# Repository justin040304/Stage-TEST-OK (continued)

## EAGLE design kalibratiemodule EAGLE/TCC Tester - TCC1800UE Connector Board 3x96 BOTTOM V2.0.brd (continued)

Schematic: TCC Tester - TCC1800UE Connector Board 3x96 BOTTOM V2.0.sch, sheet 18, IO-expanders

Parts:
C40, C41: 100nF; C0603
IC1, IC2: MCP23017SO; SO28W
R124, R125, R126, R127, R128, R129, R130, R131, R132, R133, R134, R135: 0R; R0603
R136, R137, R138, R139, R140, R141, R142, R143, R144, R145, R146, R147, R148, R149, R150, R151, R190: 10K; R0603
TP3, TP4, TP5, TP6, TP7, TP8, TP9, TP10, TP11, TP12, TP13, TP14, TP15, TP16, TP19: PTR1TP13R; TP13R

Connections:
+3.3V: C40.1, C41.1, IC1.9 (VDD), IC1.18 (!RESET), IC2.9 (VDD), IC2.18 (!RESET), R124.2, R125.2, R126.2, R130.2, R131.2, R132.2, R136.2, R137.2, R138.2, R139.2, R140.2, R141.2, R142.2, R143.2, R144.2, R145.2, R146.2, R147.2, R148.2, R149.2, R150.2, R151.2, R190.2; also elsewhere on the board
GND: C40.2, C41.2, IC1.10 (VSS), IC2.10 (VSS), R127.2, R128.2, R129.2, R133.2, R134.2, R135.2; also elsewhere on the board
unnamed: IC1.22 (GPA1), TP3.TP
unnamed: IC1.23 (GPA2), TP19.TP
unnamed: IC1.25 (GPA4), TP5.TP
unnamed: IC1.26 (GPA5), TP6.TP
unnamed: IC1.27 (GPA6), TP7.TP
unnamed: IC1.28 (GPA7), TP8.TP
unnamed: IC1.1 (GPB0), TP9.TP
unnamed: IC1.2 (GPB1), TP10.TP
unnamed: IC1.3 (GPB2), TP11.TP
unnamed: IC1.4 (GPB3), TP12.TP
unnamed: IC1.5 (GPB4), TP13.TP
unnamed: IC1.6 (GPB5), TP14.TP
unnamed: IC1.7 (GPB6), TP15.TP
unnamed: IC1.8 (GPB7), TP16.TP
unnamed: IC1.24 (GPA3), TP4.TP
unnamed: IC2.15 (A0), R126.1, R127.1
unnamed: IC2.16 (A1), R124.1, R128.1
unnamed: IC2.17 (A2), R125.1, R129.1
unnamed: IC1.15 (A0), R132.1, R133.1
unnamed: IC1.16 (A1), R130.1, R134.1
unnamed: IC1.17 (A2), R131.1, R135.1
SCL3.3V1: IC1.12 (SCL), IC2.12 (SCL); also elsewhere on the board
SDA3.3V1: IC1.13 (SDA), IC2.13 (SDA); also elsewhere on the board
SS1.1: IC2.21 (GPA0), R136.1; also elsewhere on the board
SS1.2: IC2.22 (GPA1), R137.1; also elsewhere on the board
SS1.3: IC2.23 (GPA2), R138.1; also elsewhere on the board
SS1.4: IC2.24 (GPA3), R139.1; also elsewhere on the board
SS1.5: IC2.25 (GPA4), R140.1; also elsewhere on the board
SS1.6: IC2.26 (GPA5), R141.1; also elsewhere on the board
SS1.7: IC2.27 (GPA6), R142.1; also elsewhere on the board
SS1.8: IC2.28 (GPA7), R143.1; also elsewhere on the board
SS1.9: IC2.1 (GPB0), R144.1; also elsewhere on the board
SS1.10: IC2.2 (GPB1), R145.1; also elsewhere on the board
SS1.11: IC2.3 (GPB2), R146.1; also elsewhere on the board
SS1.12: IC2.4 (GPB3), R147.1; also elsewhere on the board
SS1.13: IC2.5 (GPB4), R148.1; also elsewhere on the board
SS1.14: IC2.6 (GPB5), R149.1; also elsewhere on the board
SS1.15: IC2.7 (GPB6), R150.1; also elsewhere on the board
SS1.16: IC2.8 (GPB7), R151.1; also elsewhere on the board
SS1.17: IC1.21 (GPA0), R190.1; also elsewhere on the board

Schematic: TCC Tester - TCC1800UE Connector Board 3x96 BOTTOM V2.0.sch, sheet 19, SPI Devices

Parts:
C20, C21: 100nF; C0603
R11: 10K; R0603
U6: TXB0104D; SOIC127P600X175-14N

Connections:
5V: C21.1, U6.14 (VCCB); also elsewhere on the board
+3.3V: C20.1, R11.2, U6.1 (VCCA); also elsewhere on the board
GND: C20.2, C21.2, U6.7 (GND); also elsewhere on the board
MISO2-3.3V: U6.2 (A1); also elsewhere on the board
MISO2-5V: U6.13 (B1); also elsewhere on the board
MOSI2-3.3V: U6.3 (A2); also elsewhere on the board
MOSI2-5V: U6.12 (B2); also elsewhere on the board
SCK2-3.3V: U6.4 (A3); also elsewhere on the board
SCK2-5V: U6.11 (B3); also elsewhere on the board
SPI2_OE: R11.1, U6.8 (OE); also elsewhere on the board
SS2.1-3.3V: U6.5 (A4); also elsewhere on the board
SS2.1-5V: U6.10 (B4); also elsewhere on the board

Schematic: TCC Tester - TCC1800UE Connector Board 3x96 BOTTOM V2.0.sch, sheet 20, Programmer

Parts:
C49: DNP (100nF); C0603
C50, C51, C52, C53, C54, C55, C59, C60: 100nF; C0603
C56: 10uF; C0603
C57, C58: 30pF; C0603
CN8: USB_CONNECTORUSB_A_S_RA_SMT; MULTICOMP_USB_A_S_RA_SMT
J2: RJ11-2L-B; RJ11-NO_SHIELD
LED89, LED90, LED91, LED92: LEDCHIPLED_0805; CHIPLED_0805
R186: 10K; R0603
R187: 200R; R0603
R188, R189, R191, R192: 2.2K; R0603
R193: 0R; R0603
R_PGC: RELAY-SPDT; SPDT_TE_PE014*
R_PGD: RELAY-SPDT; SPDT_TE_PE014*
R_VPP: RELAY-SPDT; SPDT_TE_PE014*
S2: DNP; TACTILE-PTH
U$27: PICKIT3_HOLDER; PICKIT3_HOLDER_STL_100X49_V01
U$91: PIC24FJ256GA110-I/PT; QFP40P1400X1400X120-100N
U$92: TSX-3225; SMD,3.2MM_X_2.5MM
U$93: MAX4820; TSSOP20

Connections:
5V: C60.1, LED89.A, LED90.A, LED91.A, R193.1, R_PGC.1 (A1), R_PGD.1 (A1), R_VPP.1 (A1), U$93.1 (VCC), U$93.15 (COM); also elsewhere on the board
+3.3V: C50.1, C51.1, C52.1, C53.1, C54.1, C55.1, C59.1, J2.2, R186.2, U$27.2 (VDD), U$91.2 (VDD_2), U$91.16 (VDD_3), U$91.29 (PMA6/VREF+/CN42/RA10), U$91.30 (AVDD), U$91.37 (VDD_4), U$91.46 (VDD_5), U$91.62 (VDD), U$91.86 (ENVREG); also elsewhere on the board
GND: C49.2, C50.2, C51.2, C52.2, C53.2, C54.2, C55.2, C56.2, C57.2, C58.2, C59.2, C60.2, CN8.4 (GND), CN8.SHIELD@1 (SHIELD), CN8.SHIELD@2 (SHIELD), J2.3, R192.2, S2.1, U$27.3 (VSS), U$91.15 (VSS), U$91.28 (VREF-/CN41/PMA7/RA9), U$91.31 (AVSS), U$91.36 (VSS_3), U$91.45 (VSS_5), U$91.65 (VSS_2), U$91.75 (VSS_4), U$92.2, U$92.4, U$93.9 (GND), U$93.12 (PGND), U$93.18 (PGND); also elsewhere on the board
MCLR2: C49.1, R186.1, R187.2, R_VPP.11, S2.3
MOSI1: U$93.5 (DIN); also elsewhere on the board
unnamed: R187.1, U$91.13 (~MCLR)
unnamed: C57.1, U$91.63 (OSC1/CLKI/CN23/RC12), U$92.1
unnamed: C58.1, U$91.64 (OSC2/CLKO/CN22/RC15), U$92.3
unnamed: R188.2, R_PGC.2 (A2), U$93.20 (OUT1)
unnamed: C56.1, U$91.85 (VCAP/VDDCORE)
unnamed: LED92.C, R192.1
unnamed: R_VPP.14, U$27.1 (!MCLR!_VPP)
unnamed: R_PGD.14, U$27.4 (PGD)
unnamed: LED92.A, U$91.99 (CN61/PMD3/RE3)
unnamed: LED89.C, R188.1
unnamed: LED90.C, R189.1
unnamed: R_PGC.14, U$27.5 (PGC)
unnamed: R193.2, U$93.2 (SET), U$93.3 (RESET)
unnamed: LED91.C, R191.1
unnamed: R191.2, R_VPP.2 (A2), U$93.17 (OUT3)
unnamed: R189.2, R_PGD.2 (A2), U$93.19 (OUT2)
PGEC2: R_PGC.11, U$91.24 (PGEC1/AN1/RP1/CN3/RB1)
PGED2: R_PGD.11, U$91.25 (PGED1/AN0/RP0/CN2/RB0)
PGM_CLK_1: J2.5, R_PGC.12; also elsewhere on the board
PGM_DATA_1: J2.4, R_PGD.12; also elsewhere on the board
PGM_VPP_1: J2.1, R_VPP.12; also elsewhere on the board
SCK1: U$93.6 (CLK); also elsewhere on the board
SS1.16: U$93.4 (CS); also elsewhere on the board
USB_D+: CN8.3 (D+); also elsewhere on the board
USB_D-: CN8.2 (D-); also elsewhere on the board
USB_VBUS: CN8.1 (VBUS); also elsewhere on the board

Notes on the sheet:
MICROCONTROLLER FOR TESTING PROGRAMMER
USB A Connector for PICKIT3
Programmer header for external use of programmer

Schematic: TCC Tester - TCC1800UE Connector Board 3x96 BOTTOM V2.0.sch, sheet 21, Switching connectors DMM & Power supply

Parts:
C13: 100nF; C0603
CN1, CN2, CN3, CN4: HIRSCHMANN_972358700_4MM_SOCKET
CN5: BNC_5-1634506-1; BNC_TYCO_5-1634506-1
LED1, LED2, LED3, LED94, LED95, LED96, LED114, LED115: LEDCHIPLED_0805; CHIPLED_0805
R20: 2K 500mW; R0805
R22: 94K; R0603
R23, R24, R26, R111, R113, R114, R183, R184: 2.2K; R0603
R175, R182: 0R; R0603
R_FLUKE_COMMON1: RELAY-SPDT; SPDT_TE_PE014*
R_FLUKE_GND: RELAY-SPDT; SPDT_TE_PE014*
R_FLUKE_VOLTAGE+: RELAY-SPDT; SPDT_TE_PE014*
R_KEITHLEY_VOLTAGE+: RELAY-SPDT; SPDT_TE_PE014*
R_KEITHLEY_VOLTAGE+_OPEN-DRAIN: RELAY-SPDT; SPDT_TE_PE014*
R_VOLTAGE_MEASUREMENT: RELAY-SPDT; SPDT_TE_PE014*
R_VOLTAGE_MEASUREMENT_GROUP1, R_VOLTAGE_MEASUREMENT_GROUP4: RELAY-SPDT; SPDT_TE_PE014*
U$158: MAX4820; TSSOP20

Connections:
5V: C13.1, LED1.A, LED2.A, LED3.A, LED94.A, LED95.A, LED96.A, LED114.A, LED115.A, R175.1, R_FLUKE_COMMON1.1 (A1), R_FLUKE_GND.1 (A1), R_FLUKE_VOLTAGE+.1 (A1), R_KEITHLEY_VOLTAGE+.1 (A1), R_KEITHLEY_VOLTAGE+_OPEN-DRAIN.1 (A1), R_VOLTAGE_MEASUREMENT.1 (A1), R_VOLTAGE_MEASUREMENT_GROUP1.1 (A1), R_VOLTAGE_MEASUREMENT_GROUP4.1 (A1), U$158.1 (VCC), U$158.15 (COM); also elsewhere on the board
FLUKE_COMMON1: R_FLUKE_COMMON1.11; also elsewhere on the board
FLUKE_VOLTAGE+: R_FLUKE_VOLTAGE+.11, R_VOLTAGE_MEASUREMENT.11, R_VOLTAGE_MEASUREMENT_GROUP1.11, R_VOLTAGE_MEASUREMENT_GROUP4.11; also elsewhere on the board
GND: C13.2, CN2.P$1, R20.2, R22.2, R182.2, R_FLUKE_GND.11, U$158.9 (GND), U$158.12 (PGND), U$158.18 (PGND); also elsewhere on the board
KEITHLEY_VOLTAGE+: R_KEITHLEY_VOLTAGE+.11; also elsewhere on the board
KEITHLEY_VOLTAGE+_OPEN-DRAIN: R_KEITHLEY_VOLTAGE+_OPEN-DRAIN.11; also elsewhere on the board
MOSI1: U$158.5 (DIN); also elsewhere on the board
unnamed: R23.2, R_VOLTAGE_MEASUREMENT.2 (A2), U$158.13 (OUT6)
unnamed: R24.2, R_VOLTAGE_MEASUREMENT_GROUP4.2 (A2), U$158.11 (OUT7)
unnamed: R22.1, R_VOLTAGE_MEASUREMENT.14
unnamed: LED1.C, R23.1
unnamed: LED2.C, R24.1
unnamed: R20.1, R_VOLTAGE_MEASUREMENT_GROUP4.14
unnamed: R26.2, R_VOLTAGE_MEASUREMENT_GROUP1.2 (A2), U$158.10 (OUT8)
unnamed: CN3.P$1, R_VOLTAGE_MEASUREMENT_GROUP1.14
unnamed: LED3.C, R26.1
unnamed: R175.2, U$158.2 (SET), U$158.3 (RESET)
unnamed: CN5.GND2 (GND), R_FLUKE_COMMON1.14, R_FLUKE_GND.14
unnamed: R113.2, R_FLUKE_COMMON1.2 (A2), U$158.16 (OUT4)
unnamed: R114.2, R_FLUKE_GND.2 (A2), U$158.14 (OUT5)
unnamed: LED94.C, R111.1
unnamed: CN5.A, R_FLUKE_VOLTAGE+.14
unnamed: R111.2, R_FLUKE_VOLTAGE+.2 (A2), U$158.17 (OUT3)
unnamed: LED95.C, R113.1
unnamed: LED96.C, R114.1
unnamed: R184.2, R_KEITHLEY_VOLTAGE+.2 (A2), U$158.20 (OUT1)
unnamed: CN1.P$1, R_KEITHLEY_VOLTAGE+.14, R_KEITHLEY_VOLTAGE+_OPEN-DRAIN.14
unnamed: R183.2, R_KEITHLEY_VOLTAGE+_OPEN-DRAIN.2 (A2), U$158.19 (OUT2)
unnamed: LED115.C, R184.1
unnamed: LED114.C, R183.1
unnamed: CN4.P$1, R182.1
SCK1: U$158.6 (CLK); also elsewhere on the board
SS1.17: U$158.4 (CS); also elsewhere on the board

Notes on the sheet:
KEITHLEY GND
FLUKE GND
POWER RESISTOR OR ELECTRONIC LOAD
FLUKE_GND

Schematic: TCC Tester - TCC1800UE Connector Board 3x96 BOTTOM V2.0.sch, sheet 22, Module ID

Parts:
C201, C202: 100nF/50V; C0805
C203: 100pF/25V; C0805
R201: 100R; R0805
RA0, RA1: 10K; R0805
RB0, RB1: 10K; R0805
RC0, RC1: 10K; R0805
RD0, RD1: 10K; R0805
RE0, RE1: 10K; R0805
RF0, RF1: 10K; R0805
RG0, RG1: 10K; R0805
RH0, RH1: 10K; R0805
RI0, RI1: 10K; R0805
RJ0, RJ1: 10K; R0805
RK0, RK1: 10K; R0805
RL0, RL1: 10K; R0805
RM0, RM1: 10K; R0805
RN0, RN1: 10K; R0805
U1, U2: 74HC165D; SO16
U$4, U$6, U$7, U$8, U$9, U$10: 3.4; DRILL_HOLE_SPA

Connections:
5V: C201.1, C202.1, RA1.2, RB1.2, RC1.2, RD1.2, RE1.2, RF1.2, RG1.2, RH1.2, RI1.2, RJ1.2, RK1.2, RL1.2, RM1.2, RN1.2, U1.6 (H), U1.16 (VCC), U2.16 (VCC); also elsewhere on the board
C_EXT_CLK: R201.2; also elsewhere on the board
C_EXT_IN: U1.9 (QH); also elsewhere on the board
C_EXT_LOAD: U1.1 (SH/!LD), U2.1 (SH/!LD); also elsewhere on the board
GND: C201.2, C202.2, C203.2, RA0.1, RB0.1, RC0.1, RD0.1, RE0.1, RF0.1, RG0.1, RH0.1, RI0.1, RJ0.1, RK0.1, RL0.1, RM0.1, RN0.1, U1.8 (GND), U1.15 (INH), U2.6 (H), U2.8 (GND), U2.10 (SER), U2.15 (INH); also elsewhere on the board
ID_A: RA0.2, RA1.1, U1.11 (A)
ID_A1: RH0.2, RH1.1, U2.11 (A)
ID_B: RB0.2, RB1.1, U1.12 (B)
ID_B1: RI0.2, RI1.1, U2.12 (B)
ID_C: RC0.2, RC1.1, U1.13 (C)
ID_C1: RJ0.2, RJ1.1, U2.13 (C)
ID_D: RD0.2, RD1.1, U1.14 (D)
ID_D1: RK0.2, RK1.1, U2.14 (D)
ID_E: RE0.2, RE1.1, U1.3 (E)
ID_E1: RL0.2, RL1.1, U2.3 (E)
ID_F: RF0.2, RF1.1, U1.4 (F)
ID_F1: RM0.2, RM1.1, U2.4 (F)
ID_SCK_BIS: C203.1, R201.1, U1.2 (CLK), U2.2 (CLK)
unnamed: RG0.2, RG1.1, U1.5 (G)
unnamed: RN0.2, RN1.1, U2.5 (G)
unnamed: U1.10 (SER), U2.9 (QH)

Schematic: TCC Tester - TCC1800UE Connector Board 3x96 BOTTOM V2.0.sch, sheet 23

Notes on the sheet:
TODO:

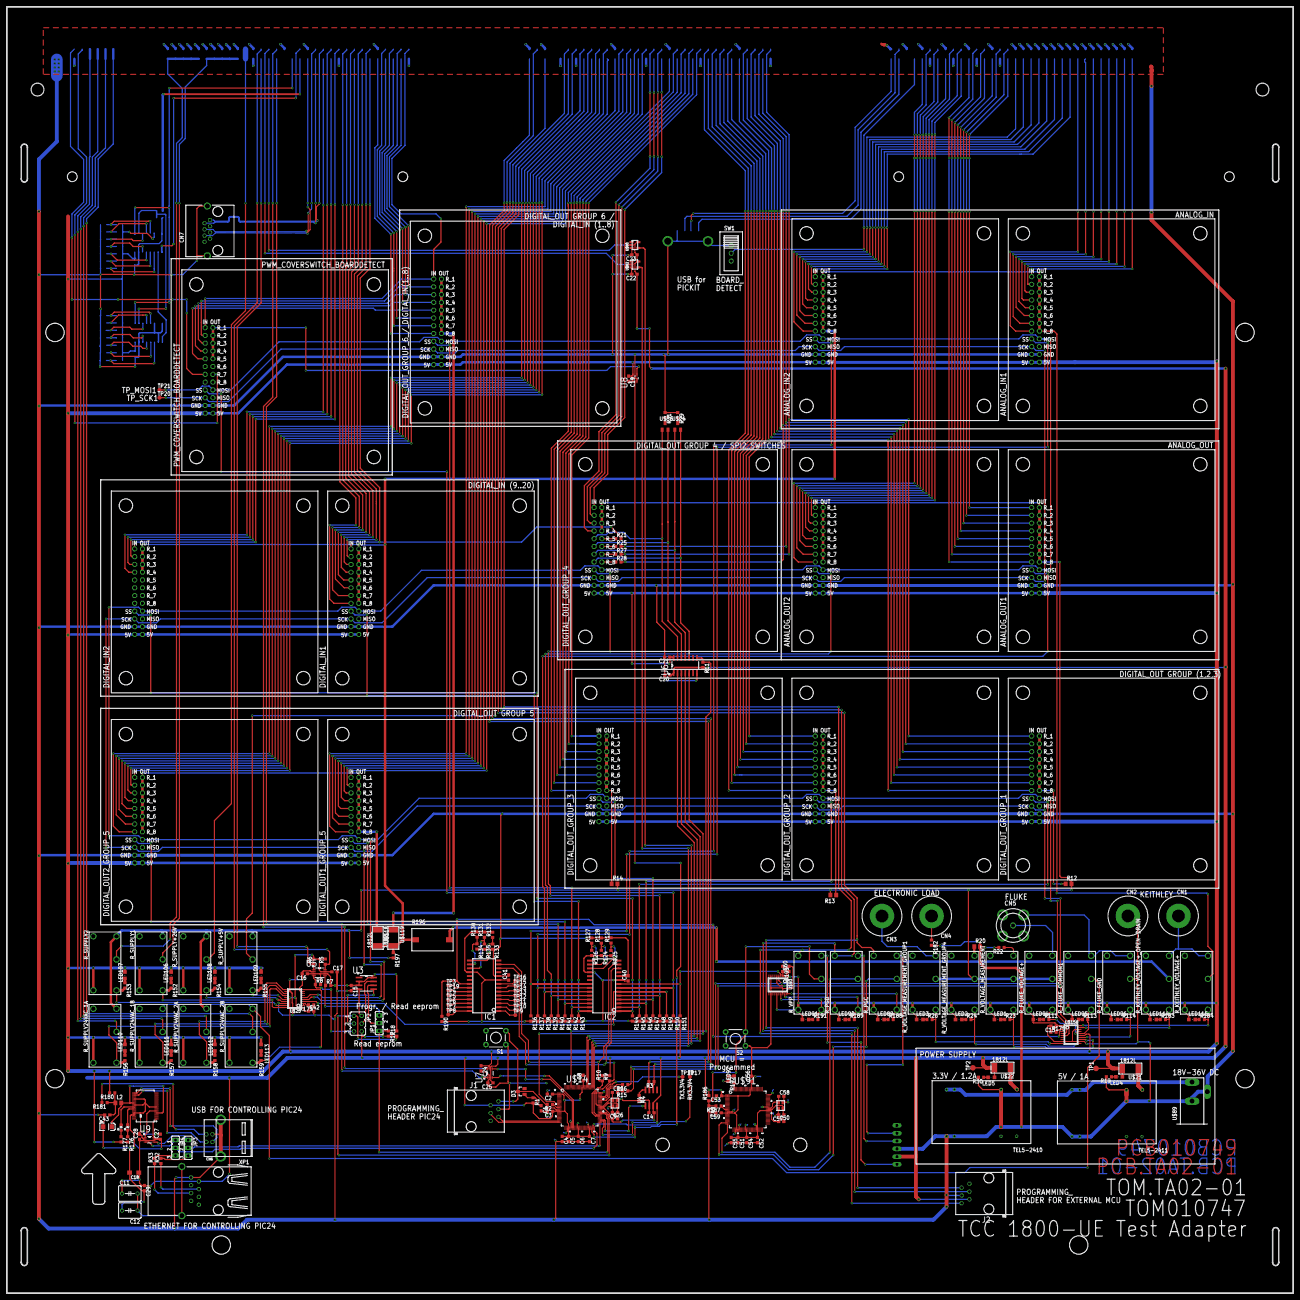
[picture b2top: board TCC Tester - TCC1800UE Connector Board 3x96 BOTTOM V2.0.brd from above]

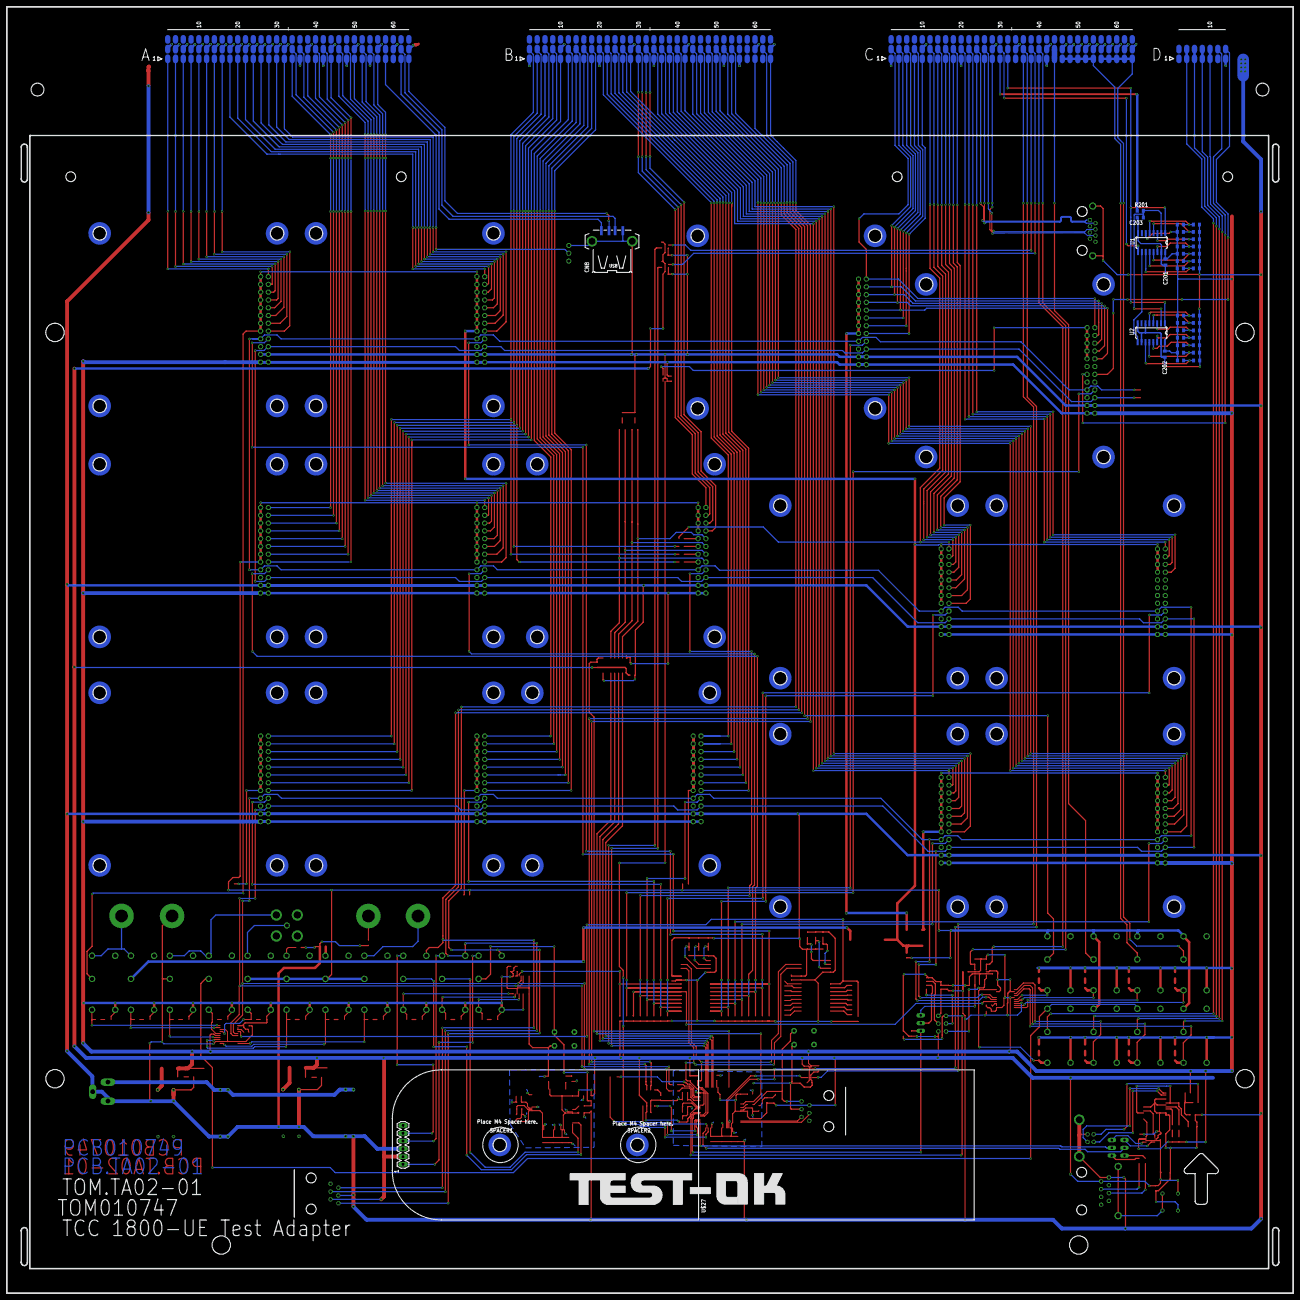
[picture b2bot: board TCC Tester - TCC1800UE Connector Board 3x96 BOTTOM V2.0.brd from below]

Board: 2 copper layers, 420.0 x 420.0 mm, 313 parts (38 on the bottom side), 326 nets.

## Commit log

2024-11-13 Voeg documenten toe
